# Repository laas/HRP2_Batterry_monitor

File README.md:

# HRP2_Battery_monitor
[BOARD] measure voltage and current of each of the 2 batteries of HRP2 via INA226

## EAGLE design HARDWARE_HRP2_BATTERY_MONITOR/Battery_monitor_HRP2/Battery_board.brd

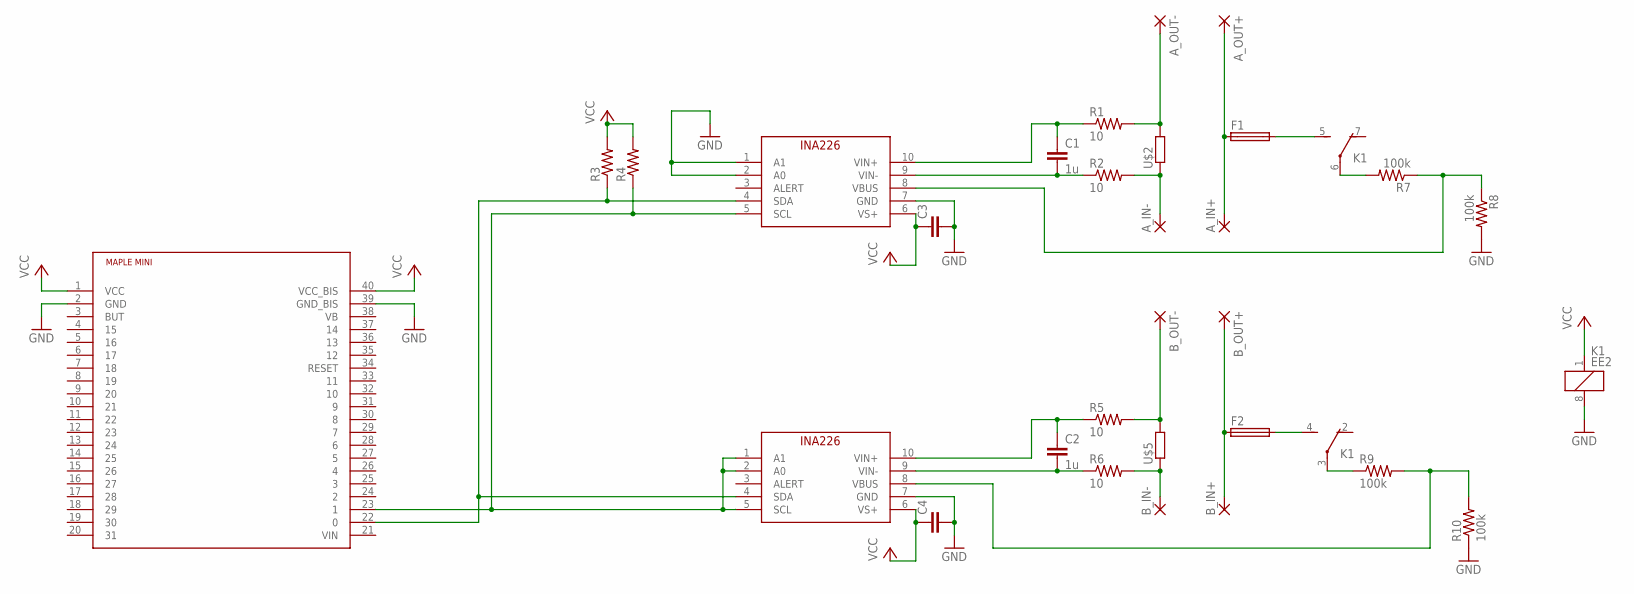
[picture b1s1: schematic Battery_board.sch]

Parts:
A_IN+: WIREPAD4,16O1,6; 4,16O1,6
A_IN-: WIREPAD4,16O1,6; 4,16O1,6
A_OUT+: WIREPAD4,16O1,6; 4,16O1,6
A_OUT-: WIREPAD4,16O1,6; 4,16O1,6
B_IN+: WIREPAD4,16O1,6; 4,16O1,6
B_IN-: WIREPAD4,16O1,6; 4,16O1,6
B_OUT+: WIREPAD4,16O1,6; 4,16O1,6
B_OUT-: WIREPAD4,16O1,6; 4,16O1,6
C1, C2: 1u; C0603
C3, C4: CC0603; C0603
F1, F2: TE5
K1: EE2; EE2-5NU
R1, R2, R5, R6: 10; R0603
R3, R4: R-US_R0603; R0603
R7, R8, R9, R10: 100k; R1206
U$1, U$4: INA226; MSOP10
U$2, U$5: R_SHUNT_2526; R2526
U$3: MAPLE_MINI; DIL40_MAPLE

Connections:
GND: C3.2, C4.2, K1.8 (2), R8.2, R10.1, U$1.1 (A1), U$1.2 (A0), U$1.7 (GND), U$3.2 (GND), U$3.39 (GND_BIS), U$4.7 (GND)
unnamed: R4.1, U$1.5 (SCL), U$3.23 (1), U$4.1 (A1), U$4.2 (A0), U$4.5 (SCL)
unnamed: C1.1, R1.1, U$1.10 (VIN+)
unnamed: C1.2, R2.1, U$1.9 (VIN-)
unnamed: F1.2, K1.5 (S)
unnamed: A_OUT-.1, R1.2, U$2.2
unnamed: A_IN-.1, R2.2, U$2.1
unnamed: A_IN+.1, A_OUT+.1, F1.1
unnamed: F2.2, K1.4 (S)
unnamed: C2.1, R5.1, U$4.10 (VIN+)
unnamed: C2.2, R6.1, U$4.9 (VIN-)
unnamed: R3.1, U$1.4 (SDA), U$3.22 (0), U$4.4 (SDA)
unnamed: B_OUT-.1, R5.2, U$5.2
unnamed: B_IN-.1, R6.2, U$5.1
unnamed: B_IN+.1, B_OUT+.1, F2.1
unnamed: K1.3, R9.1
unnamed: R9.2, R10.2, U$4.8 (VBUS)
unnamed: K1.6, R7.2
unnamed: R7.1, R8.1, U$1.8 (VBUS)
VCC: C3.1, C4.1, K1.1, R3.2, R4.2, U$1.6 (VS+), U$3.1 (VCC), U$3.40 (VCC_BIS), U$4.6 (VS+)

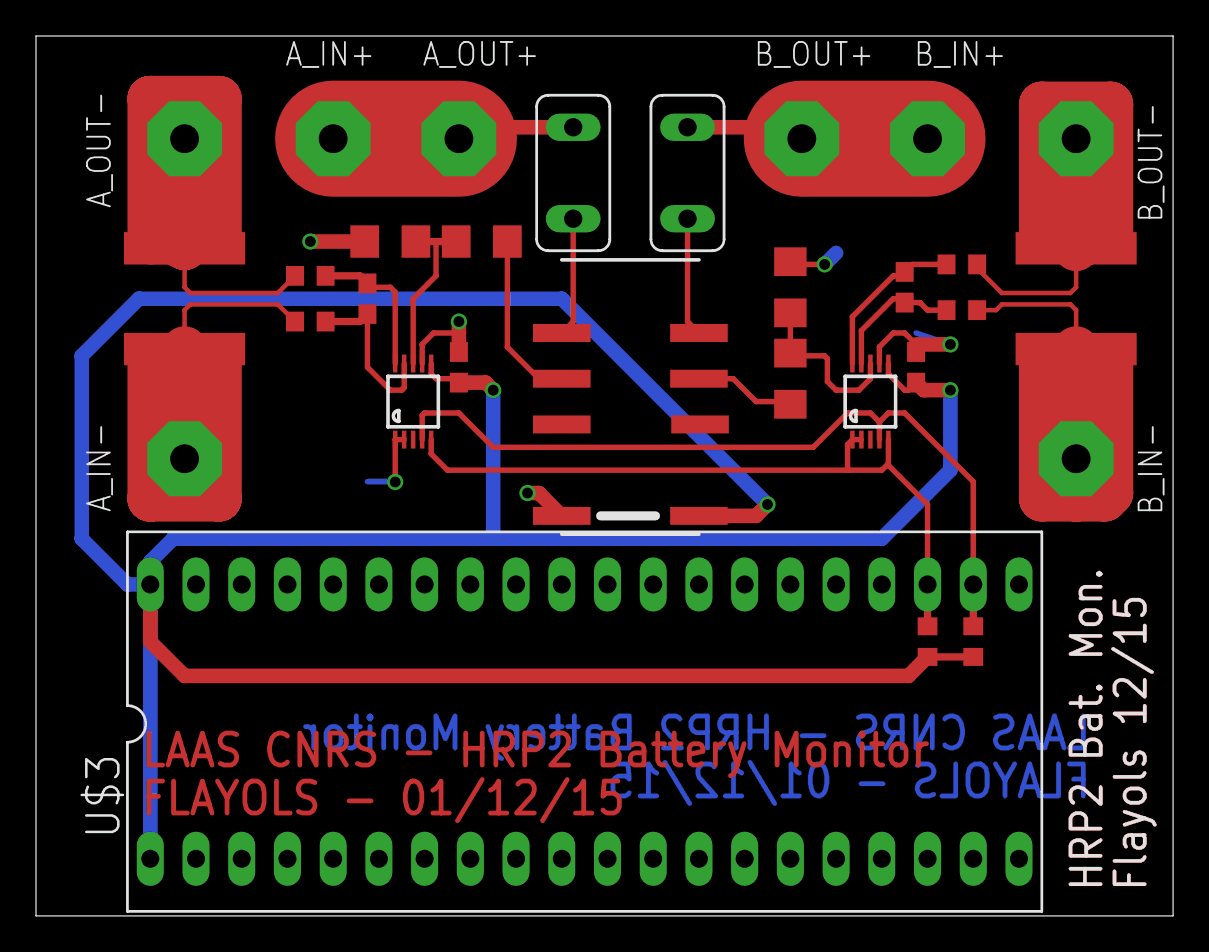
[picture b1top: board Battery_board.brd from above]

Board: 2 copper layers, 63.2 x 48.9 mm, 30 parts (0 on the bottom side), 20 nets.

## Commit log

2016-01-11 first version of compilable firmware (basic blink)
2016-01-11 Add INA226 Library - Read sensor value and send it via USB in readable format
2016-01-14 Expose register reading functions
2016-01-14 Update firmware for fast communication in RAW mode
    Add help plot
2016-01-14 Make a python example of use
2016-01-14 Make a standard C, UNIX example
2016-01-18 update help message
2016-01-18 minor changes
2016-01-18 Add eagle board design files in HARDWARE
2016-01-19 AJUST CALIBRATION VALUES - SHOW CURRENT
    Using a resistive charge and measure current and voltage reference given by a mx556 multimeter
    no noise measurement done yet.
2016-01-27 Add a simple loging program (for first experiments on the robot)
2016-01-27 fix bug
2016-02-10 add wiring.png
